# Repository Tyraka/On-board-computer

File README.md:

# On-board computer

## About
first version of rocket on-board computer. Main task of this computer is save the flight telemtry to txt file on micro sd card. Second task is notice when rocket starts falling down and open the parachute.

- [On-board computer](#on-board-computer)
  * [About](#about)
  *  [PCB](#pcb)
      - [Schema](#schema)
      - [Board](#board)
      - [Libraries](#libraries)
  * [Sensors](#sensors)
      - [SD-card](#sd-card)
      - [GPS](#gps)
      - [BMP 280](#bmp-280)
      - [Pin map](#pin-map)
  * [Code for arduino](#code-for-arduino)

  ## PCB
  Circut board is designed in Eagle

  ### Schema
  Schema of <br/>
  [schema of on-board computer](https://github.com/WiciuTyraka/On-board-computer/blob/master/PCB/Schema/tyraka.sch)

  ### Board
  links for downloading a board file.
  - [link for tyraka.brd](https://github.com/WiciuTyraka/On-board-computer/blob/master/PCB/Board/tyraka.brd)

  ### Libraries
  Here are a necessary libraries for elements thats are used in project.
  - [BMP 280](https://github.com/WiciuTyraka/On-board-computer/blob/master/PCB/lib/111_BAROMETR.lbr)
  - [GPS](https://github.com/WiciuTyraka/On-board-computer/blob/master/PCB/lib/111_gps_tyraka.lbr)
  - [microsd](https://github.com/WiciuTyraka/On-board-computer/blob/master/PCB/lib/111_microsd.lbr)

  ## Sensors
Here you can find description of all sensors are used in project

  ### SD-card
  ---
  Micro sd-card adapter is used for saving all data in txt file or as a json.
  <details>
  <summary>details</summary>
  </br>

  #### Wireing schema
  This is the schema for all the wireing with arduino

  #### Adapter wireing
  | MicroSD Card Adapter | Adruino UNO Pin |
  |----------------------|----------------:|
  |          CS          |        4        |
  |          SCK         |        13       |
  |          MOSI        |        11       |
  |          MISO        |        12       |
  |          VCC         |        5V       |
  |          GND         |        GND      |

  #### Arduino code
  [the necessary code is here](https://github.com/WiciuTyraka/On-board-computer/blob/master/Sensors/SD_card/SD_card.cpp)
  </details>

  ### GPS
  ---
  in project is used gy-gps6mv2 chip
  <details>
  <summary>details</summary>
  </br>

  #### Arduino wireing
  | MicroSD Card Adapter | Adruino UNO Pin |
  |----------------------|-----------------|
  |          TX          |        2        |
  |          RX          |         3       |
  |          VCC         |        5V       |
  |          GND         |        GND      |

  #### GPS Tiny library
  You can download the necessary library here:
 [download](https://github.com/WiciuTyraka/On-board-computer/tree/master/Sensors/GPS/TinyGPS-13)

  #### Arduino code
  [the necessary code is here](https://github.com/WiciuTyraka/On-board-computer/blob/master/Sensors/GPS/gps_basic.cpp)

  #### Datasheet
[link](https://www.openimpulse.com/blog/wp-content/uploads/wpsc/downloadables/GY-NEO6MV2-GPS-Module-Datasheet.pdf)
  </details>

  ### BMP280
  ---
  [bmp280](https://nettigo.pl/products/modul-10-dof-mpu9250-bmp280) is a barometer which is used to mesure flight high.
  <details>
  <summary>details</summary>
  </br>

  #### I2C Sensor library
  You can download the necessary library here:
 [download](https://github.com/WiciuTyraka/On-board-computer/tree/master/Sensors/BMP_280/I2C-Sensor-Lib_iLib)

  #### Arduino code
  [the necessary code is here](https://github.com/WiciuTyraka/On-board-computer/blob/master/Sensors/BMP_280/bmp_280.cpp)

  #### Datasheet
[link](https://github.com/WiciuTyraka/On-board-computer/blob/master/Sensors/BMP_280/BST-BMP280-DS001-11.pdf)
  </details>

  ### Pin map
---
This table contains information abaout all pins to witch are connected device

| Pin number |Device     |
|------------|---------- |
| 2          |GPS TX     |
| 3          |GPS RX     |
| 5          |PYRO       |
| 10         |SD card CS |
| 11         |MOSI       |
| 12         |MISO       |
| 13         |CLK        |
| A4         |SDA        |
| A5         |SCL        |

## Code for Arduino

This version of code not include a gyroscope.
- here you can find a [code](https://github.com/WiciuTyraka/On-board-computer/blob/master/Arduino_code/main.cpp)

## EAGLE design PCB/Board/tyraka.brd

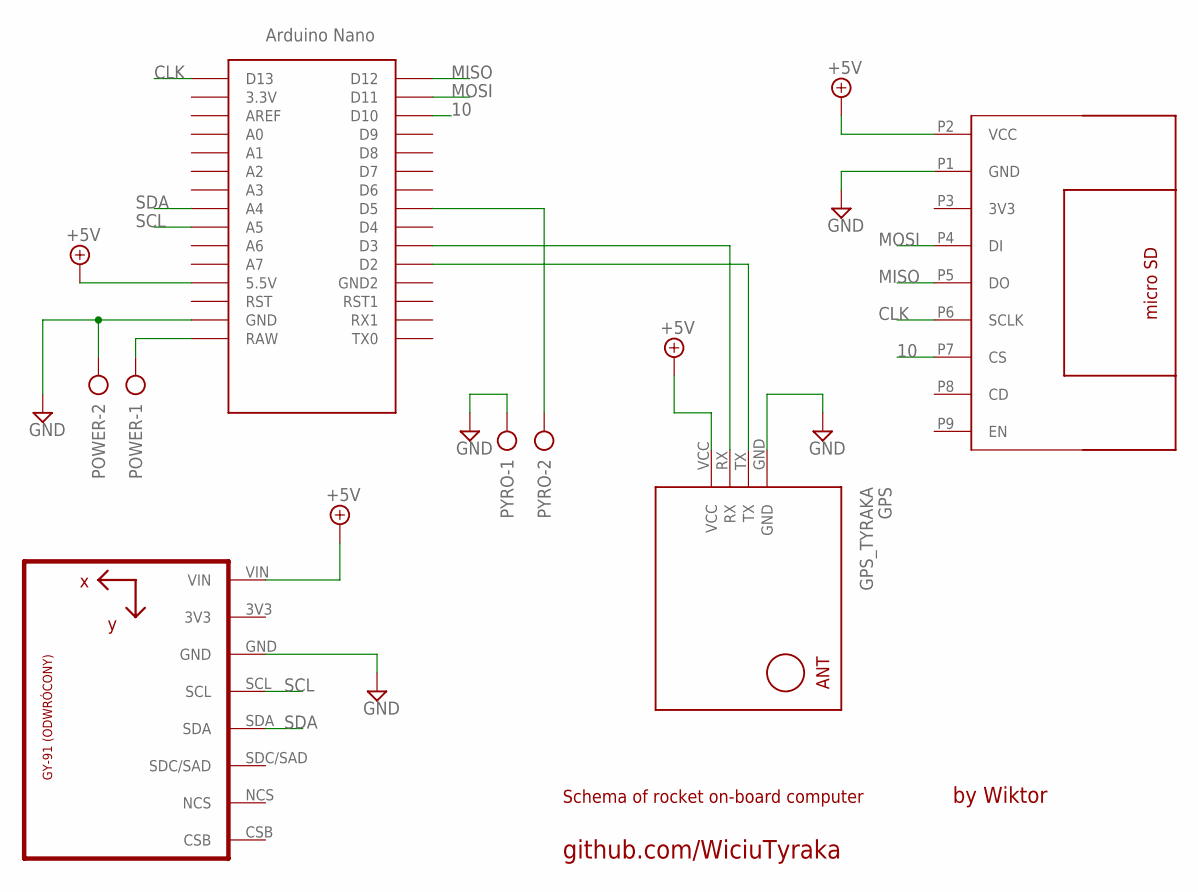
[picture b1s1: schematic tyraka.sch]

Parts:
ARDUINO: NANO
GPS: GPS_TYRAKA; GPS-RECEIVER-NEO6M
POWER: AK500/2
PYRO: AK500/2
SD1: MICRO_SD
U1: GY-521MPU6050; GY-521

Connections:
10: ARDUINO.D10, SD1.P7 (CS)
+5V: ARDUINO.5V (5.5V), GPS.VCC, SD1.P2 (VCC), U1.VIN
CLK: ARDUINO.D13, SD1.P6 (SCLK)
GND: ARDUINO.GND, GPS.GND, POWER.2, PYRO.1, SD1.P1 (GND), U1.GND
MISO: ARDUINO.D12, SD1.P5 (DO)
MOSI: ARDUINO.D11, SD1.P4 (DI)
unnamed: ARDUINO.D5, PYRO.2
unnamed: ARDUINO.D2, GPS.TX
unnamed: ARDUINO.D3, GPS.RX
RAW: ARDUINO.RAW, POWER.1
SCL: ARDUINO.A5, U1.SCL
SDA: ARDUINO.A4, U1.SDA

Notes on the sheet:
by Wiktor
Schema of rocket on-board computer
github.com/WiciuTyraka

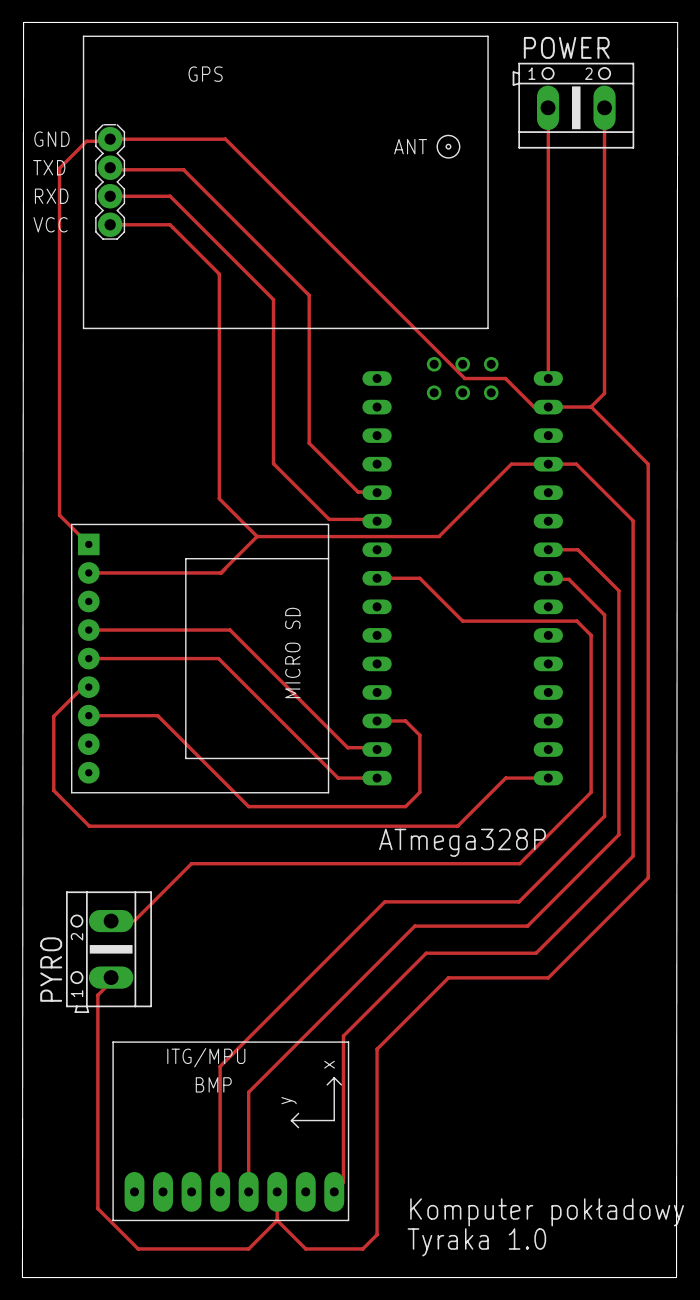
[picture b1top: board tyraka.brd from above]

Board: 2 copper layers, 58.3 x 111.7 mm, 6 parts (0 on the bottom side), 12 nets.

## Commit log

2019-05-09 add pcb
2019-05-09 add code and lib
2019-05-09 gps add
2019-05-09 readme upragde
2019-05-09 readme upgrade
